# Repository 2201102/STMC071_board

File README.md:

# 光る! マイコン搭載基板キーホルダー

マイコンとフルカラーLEDを搭載した、キーホルダーサイズのマイコンボードです。
USBケーブルを挿すだけでカラフルに光り、ボタンで発光パターンや色を変えられます。
STM32C071を搭載しているので、自分でプログラムを書き込んで好きなように遊ぶこともできます。

## 目次
- [特徴](#特徴)
- [仕様](#仕様)
- [使い方](#使い方)
- [各部説明](#各部説明)
- [注意事項](#注意事項)
- [おまけ機能](#おまけ機能)
- [改造](#改造)
- [マイコンボードとして使う](#マイコンボードとして使う)
- [回路図](#回路図)

## 特徴
1. **USBで光る**：USBケーブルを挿すとフルカラーLEDがレインボーに発光します。
2. **ボタンで変えられる**：ボタンを押すと発光パターンが変わり(全8パターン)、長押しで発光色が切り替わります。
3. **マイコンとして使える**：STM32C071を搭載。STM32の開発環境でプログラムでき、USB DFUで書き込めます(専用の書き込み器は不要です)。

## 仕様
| 項目 | 内容 |
| --- | --- |
| マイコン | STM32C071F8P6 |
| LED | フルカラーLED |
| 電源 | USB Type-C(5V) |
| 書き込み方式 | USB DFU |
| ボタン | BUTTON / BOOT / RESET の3つ |
| その他 | USB対応 |

## 使い方
1. 基板に金属が触れていないことを確認します(→[注意事項](#注意事項))。
2. USBケーブルを挿します。
3. LEDがカラフルに発光します。

### 発光パターン
BUTTON(基板上でSW2と書かれているボタン)を**単押し**すると、次のパターンに切り替わります。

1. レインボー
2. チェス
3. ナイトライダー
4. ランダム
5. イルミネーション
6. 単色
7. 点滅
8. じんわり点滅

8番目の次は、1番目に戻ります。
**長押し**すると発光色が切り替わります。

## 各部説明

### ボタン
| 名称 | 基板表記 | ピン | 役割 |
| --- | --- | --- | --- |
| BUTTON | SW2 | PA4 | プログラム用ボタン。初期状態では単押しで発光パターン変更、長押しで発光色変更。 |
| BOOT | SW3 | PA14/PA15 | 書き込み時に使用。押しながら電源ONまたはRESETで書き込みモードに入る。 |
| RESET | SW1 | PF2 | リセットボタン。押すとプログラムが最初から実行される。 |

### ピン配置
基板の両端に並ぶスルーホールから、各ピンを引き出せます。
基板の向きは上記の「各部説明」の図を基準にしています。

| 左列(上→下) | 右列(上→下) |
| --- | --- |
| 3.3V | 5V |
| PA0 | PC14 |
| PA1 | PC15 |
| PA2 | PB3 / PB4 / PB5 / PB6 |
| PA3 | PB7 / PB8 |
| PA4 | PF2 |
| PA5 | PA13 |
| PA6 | PA14 / PA15 |
| PA7 | PA8 |
| GND | GND |

> PA4(BUTTON)、PF2(RESET)、PA14/PA15(BOOT)は基板上のボタンとも接続されています。外部回路をつなぐ際は、ボタン操作と干渉しないよう注意してください。

## 注意事項
- **ショートに注意してください。** 保護素子は内蔵していますが、部品がむき出しのため、念のため金属類が接触していないことを確認してから電源を入れてください。
- **はんだ不良の可能性があります。** すべての部品を手作業で実装しているため、不良が含まれる場合があります。販売時にはキーホルダーとしての機能(ファームウェアの書き込み、LEDの発光、各ボタンの動作)のみ確認しており、それ以外の機能は未確認です。はんだ不良などがあった場合は、お手数ですが購入者様ご自身での修正をお願いします。
- **USB Type-Cは片面のみ通信できます。** コストの都合上、USBの通信は片面のみ対応です。書き込みやUSB CDCがうまくいかない場合は、ケーブルの挿す向きを変えてください。

## おまけ機能
### USB CDC(仮想シリアルポート)
USBで仮想シリアルポートを開いています。シリアルモニタが使える端末と接続すると、マイコンとコマンドをやり取りできます。
接続して`help`と送信すると、コマンド一覧が返ってきます。

## 改造
### C to Cケーブルでの給電
そのままではA to Cケーブルでのみ給電できます。
基板上部の未実装エリアに5.1kΩの抵抗を2つ実装すると、C to Cケーブルでも給電できるようになります。

## マイコンボードとして使う
このボードにはSTM32C071F8P6が載っています。STM32に対応した開発環境を使えば、好きなプログラムを書き込めます。

### 書き込み方法(USB DFU)
1. BOOTボタンを押しながら、USBケーブルを挿す(またはRESETボタンを押す)と、書き込みモードに入ります。
2. STM32CubeProgrammerを起動し、接続方式でUSBを選びます。
3. コンパイルしたバイナリを書き込みます。

書き込みにはSTM32CubeProgrammerの使用を推奨します。うまく認識されない場合は、USBの向きを変えてみてください。

### サンプルプログラム
リポジトリのsample_program内に初期ファームウェアのプロジェクトが入っています。
参考にするほか初期ファームに戻したくなった時などにご活用ください。

## 回路図

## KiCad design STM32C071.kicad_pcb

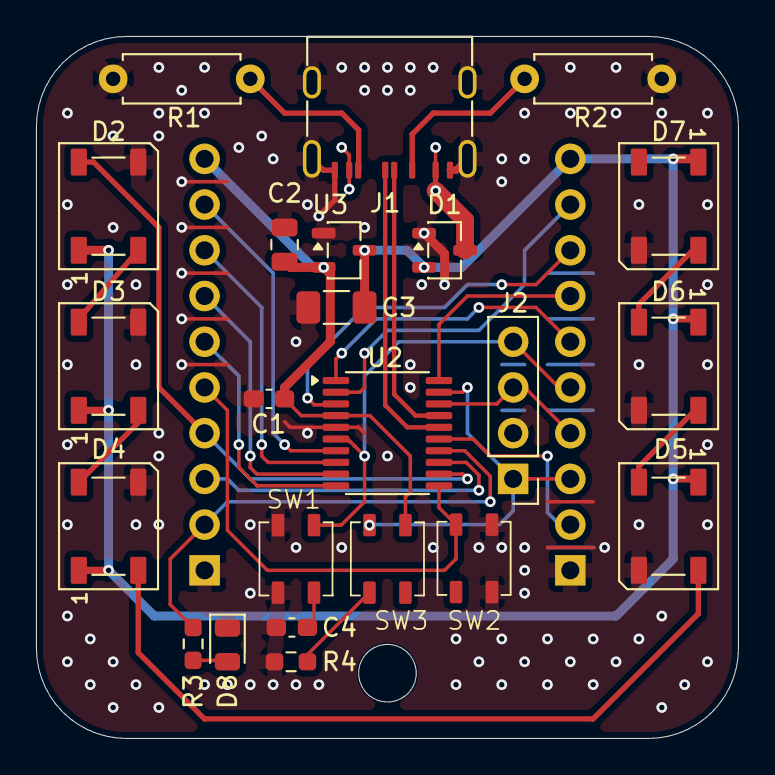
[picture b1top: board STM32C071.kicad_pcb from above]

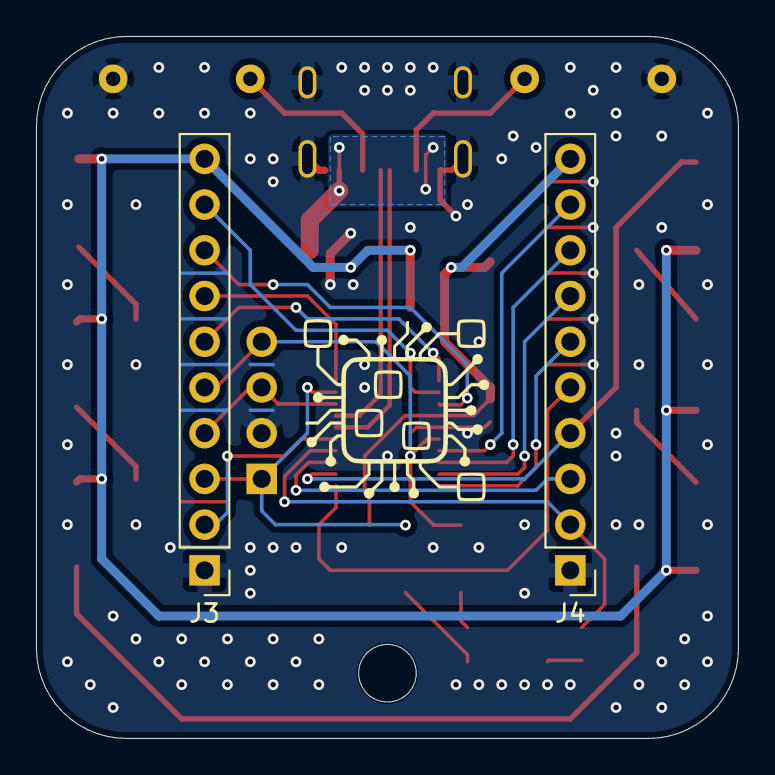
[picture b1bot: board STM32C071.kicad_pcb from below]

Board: 2 copper layers, 39.0 x 39.0 mm, 26 parts (2 on the bottom side), 30 nets.

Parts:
C1: 0.1uF; C_0603_1608Metric_Pad1.08x0.95mm_HandSolder
C2: 10uF; C_0805_2012Metric
C3: 22uF; C_1206_3216Metric_Pad1.33x1.80mm_HandSolder
C4: 100nF; C_0603_1608Metric_Pad1.08x0.95mm_HandSolder
D1: CH213K; SOT-23-3
D2, D3, D4, D5, D6, D7: WS2812B; LED_WS2812B_PLCC4_5.0x5.0mm_P3.2mm
D8: LED_Y; LED_0805_2012Metric
H1: MountingHole; MountingHole_3.2mm_M3
J1: USB_C_Receptacle_USB2.0_14P; U2CF8PA_USB_C
J2: Conn_01x04_Pin; PinHeader_1x04_P2.54mm_Vertical
J3, J4: Conn_01x10_Pin; PinHeader_1x10_P2.54mm_Vertical
R1, R2: 5.1k; R_Axial_DIN0207_L6.3mm_D2.5mm_P7.62mm_Horizontal
R3: 1k; R_0603_1608Metric_Pad0.98x0.95mm_HandSolder
R4: 10k; R_0603_1608Metric_Pad0.98x0.95mm_HandSolder
SW1, SW2, SW3: SW_Push; TS3315
U2: STM32C071F8Px; TSSOP-20_4.4x6.5mm_P0.65mm
U3: SLHT33H; SOT-23-3

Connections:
+3V3: C1.1, C2.1, J4.10, SW3.1, U2.4 (VDD), U3.2 (OUT)
+5V: C3.1, D1.2 (VO-), D2.1 (VDD), D3.1 (VDD), D4.1 (VDD), D5.1 (VDD), D6.1 (VDD), D7.1 (VDD), J3.10, U3.3 (IN)
/PA0: J4.9, U2.7 (PA0)
/PA1: J4.8, U2.8 (PA1)
/PA2: J4.7, U2.9 (PA2)
/PA3: J4.6, U2.10 (PA3)
/PA6: J4.3, U2.13 (PA6)
/PA8: J3.2, U2.15 (PA8)
/PB3/PB4/PB5/PB6: J3.7, U2.20 (PB3/PB4/PB5/PB6)
/PB7/PB8: J3.6, U2.1 (PB7/PB8)
/PC14: J3.9, U2.2 (PC14)
/PC15: J3.8, U2.3 (PC15)
GND: C1.2, C2.2, C3.2, C4.2, D1.1 (GND), D2.3 (VSS), D3.3 (VSS), D4.3 (VSS), D5.3 (VSS), D6.3 (VSS), D7.3 (VSS), D8.1 (K), J1.A12 (GND), J1.B12 (GND), J1.SH (SHIELD), J2.2, J3.1, J4.1, R1.1, R2.1, R4.2, SW1.2, SW2.2, U2.5 (VSS), U3.1 (GND)
NRST: C4.1, J2.4, J3.5, SW1.1, U2.6 (PF2)
Neopixel: D2.4 (DIN), J4.4, U2.12 (PA5)
unnamed: D1.3 (VI+), J1.A9 (VBUS), J1.B9 (VBUS)
unnamed: D2.2 (DOUT), D3.4 (DIN)
unnamed: D3.2 (DOUT), D4.4 (DIN)
unnamed: D4.2 (DOUT), D5.4 (DIN)
unnamed: D5.2 (DOUT), D6.4 (DIN)
unnamed: D6.2 (DOUT), D7.4 (DIN)
unnamed: D8.2 (A), R3.2
unnamed: J1.A5 (CC1), R2.2
unnamed: J1.B5 (CC2), R1.2
T_SWCLK: J2.1, J3.3, R4.1, SW3.2, U2.19 (PA14/PA15)
T_SWDIO: J2.3, J3.4, U2.18 (PA13)
USB_D+: J1.A6 (D+), U2.17 (PA12)
USB_D-: J1.A7 (D-), U2.16 (PA11)
USER_BUTTON: J4.5, SW2.1, U2.11 (PA4)
USER_LED: J4.2, R3.1, U2.14 (PA7)

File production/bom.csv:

Designator,Footprint,Quantity,Value,LCSC Part #
C1,0603,1,0.1uF,
C2,0805,1,10uF,C96446
C3,1206,1,22uF,C45783
C4,0603,1,100nF, C14663
D1,SOT-23-3,1,CH213K,
"D2, D3, D4, D5, D6, D7",LED_WS2812B_PLCC4_5.0x5.0mm_P3.2mm,6,WS2812B,
D8,0805,1,LED_Y,C2296
J1,U2CF8PA_USB_C,1,USB_C_Receptacle_USB2.0_14P,
J2,PinHeader_1x04_P2.54mm_Vertical,1,Conn_01x04_Pin,
"J3, J4",PinHeader_1x10_P2.54mm_Vertical,2,Conn_01x10_Pin,
"R1, R2",R_Axial_DIN0207_L6.3mm_D2.5mm_P7.62mm_Horizontal,2,5.1k,C23186
R3,0603,1,1k, C22787
R4,0603,1,10k, C25804
"SW1, SW2, SW3",TS3315,3,SW_Push,C720477
U2,TSSOP-20_4.4x6.5mm_P0.65mm,1,STM32C071F8Px,
U3,SOT-23-3,1,SLHT33H,MCP1700T-3302E/TT
